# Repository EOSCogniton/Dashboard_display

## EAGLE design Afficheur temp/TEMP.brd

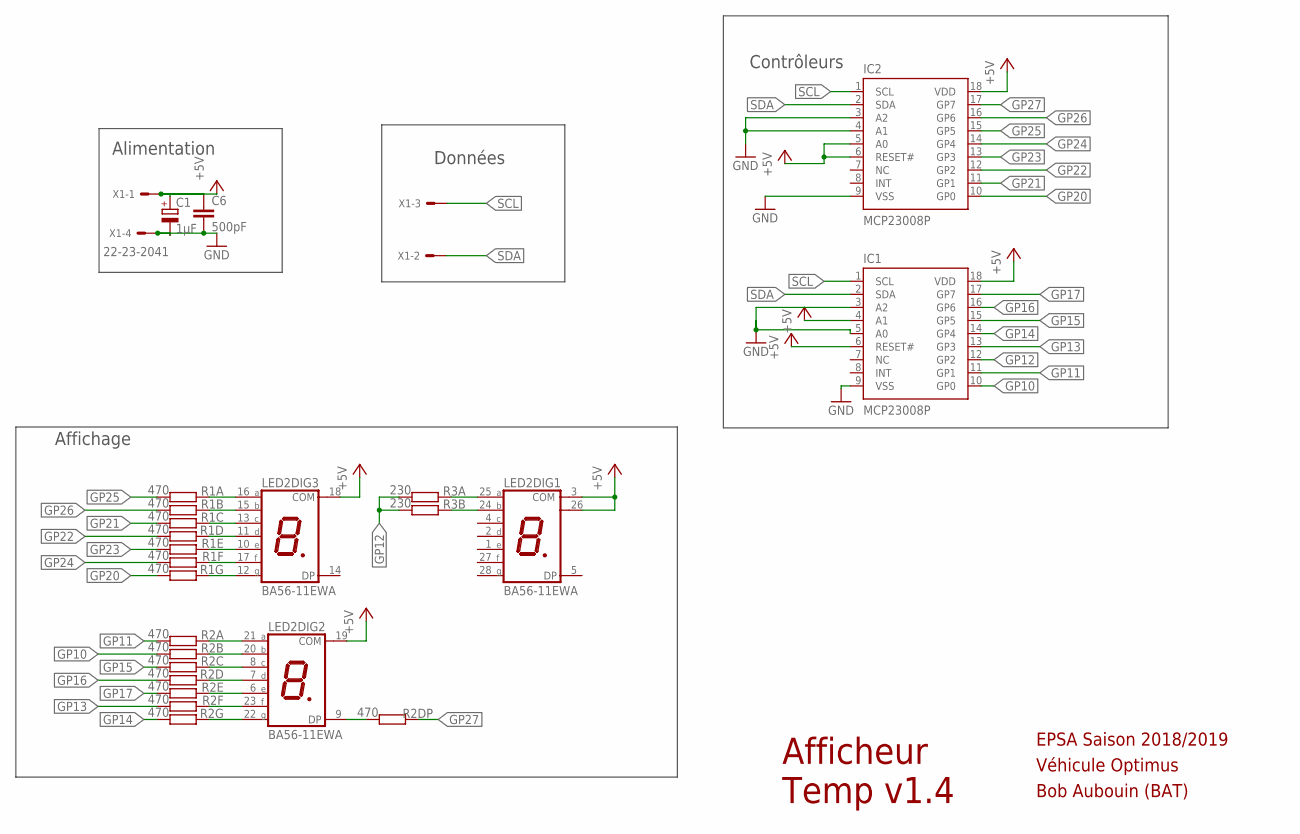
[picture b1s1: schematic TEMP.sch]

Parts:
C1: 1µF; B45181A
C6: 500pF; C025-025X050
IC1, IC2: MCP23008P; DIL18
LED2: BA56-11EWA; BA/BC56
R1A, R1B, R1C, R1D, R1E, R1F, R1G, R2A, R2B, R2C, R2D, R2DP, R2E, R2F, R2G: 470; 0204/7
R3A, R3B: 230; 0204/7
X1: 22-23-2041

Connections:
+5V: C1.+, C6.1, IC1.4 (A1), IC1.6 (RESET#), IC1.18 (VDD), IC2.5 (A0), IC2.6 (RESET#), IC2.18 (VDD), LED2.3 (COM), LED2.18 (COM), LED2.19 (COM), LED2.26 (COM), X1.1
GND: C1.-, C6.2, IC1.3 (A2), IC1.5 (A0), IC1.9 (VSS), IC2.3 (A2), IC2.4 (A1), IC2.9 (VSS), X1.4
GP10: IC1.10 (GP0), R2B.2
GP11: IC1.11 (GP1), R2A.2
GP12: IC1.12 (GP2), R3A.2, R3B.2
GP13: IC1.13 (GP3), R2F.2
GP14: IC1.14 (GP4), R2G.2
GP15: IC1.15 (GP5), R2C.2
GP16: IC1.16 (GP6), R2D.2
GP17: IC1.17 (GP7), R2E.2
GP20: IC2.10 (GP0), R1G.2
GP21: IC2.11 (GP1), R1C.2
GP22: IC2.12 (GP2), R1D.2
GP23: IC2.13 (GP3), R1E.2
GP24: IC2.14 (GP4), R1F.2
GP25: IC2.15 (GP5), R1A.2
GP26: IC2.16 (GP6), R1B.2
GP27: IC2.17 (GP7), R2DP.1
unnamed: LED2.16 (A), R1A.1
unnamed: LED2.15 (B), R1B.1
unnamed: LED2.13 (C), R1C.1
unnamed: LED2.11 (D), R1D.1
unnamed: LED2.10 (E), R1E.1
unnamed: LED2.17 (F), R1F.1
unnamed: LED2.12 (G), R1G.1
unnamed: LED2.21 (A), R2A.1
unnamed: LED2.20 (B), R2B.1
unnamed: LED2.8 (C), R2C.1
unnamed: LED2.7 (D), R2D.1
unnamed: LED2.6 (E), R2E.1
unnamed: LED2.23 (F), R2F.1
unnamed: LED2.22 (G), R2G.1
unnamed: LED2.9 (DP), R2DP.2
unnamed: LED2.24 (B), R3B.1
unnamed: LED2.25 (A), R3A.1
SCL: IC1.1 (SCL), IC2.1 (SCL), X1.3
SDA: IC1.2 (SDA), IC2.2 (SDA), X1.2

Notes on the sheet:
Afficheur Temp v1.4
EPSA Saison 2018/2019
Alimentation
Contrôleurs
Données
Affichage
Véhicule Optimus
Bob Aubouin (BAT)

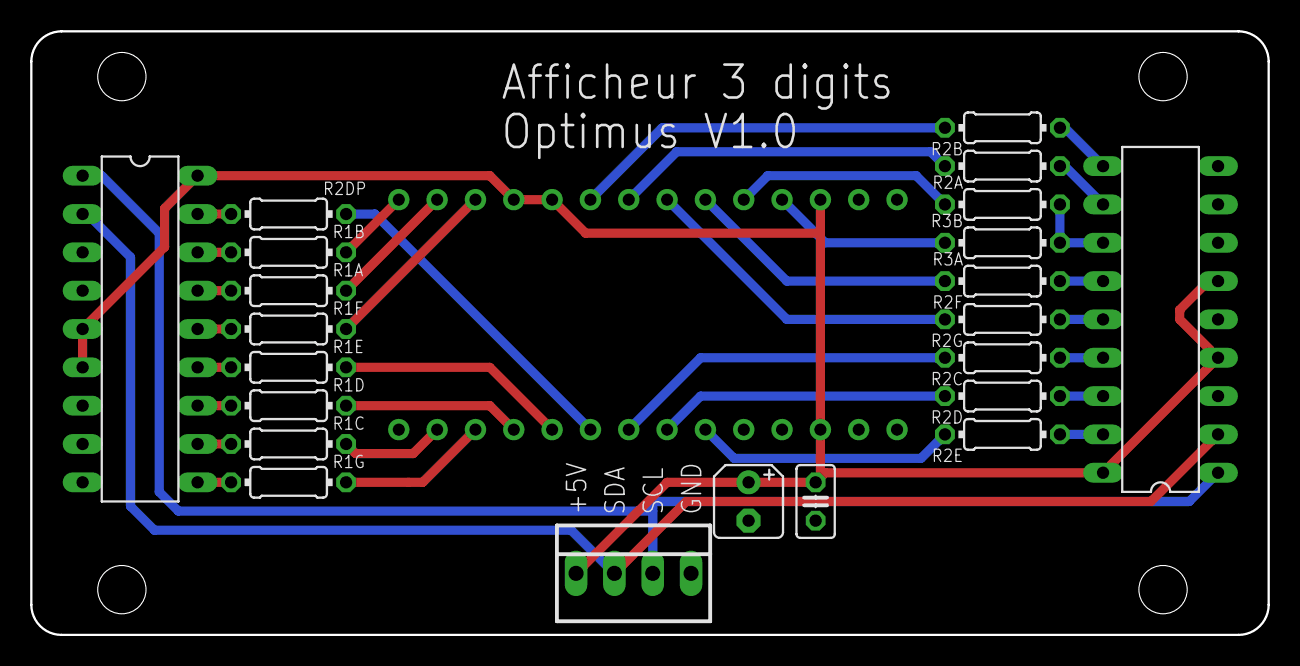
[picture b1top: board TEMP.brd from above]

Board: 2 copper layers, 82.0 x 40.0 mm, 23 parts (1 on the bottom side), 37 nets.

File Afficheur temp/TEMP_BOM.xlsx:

Qty | Value | Device | Description | Dispo au garage ? | Référence RS |  |  |  |  | oui
2 | 1k | R-EU_0204/7 | RESISTOR, European symbol | oui |  |  |  |  |  | non
1 |  | 22-23-2041 | .100 (2.54mm) Center Header - 4 Pin" | Je sais pas | 679-5596 |  |  |  |  | Je sais pas
2 | 230 | R-EU_0204/7 | RESISTOR, European symbol | oui
15 | 470 | R-EU_0204/7 | RESISTOR, European symbol | oui
1 | 500pF | C-EU025-025X050 | CAPACITOR, European symbol | Je sais pas | 831-3026
1 |  | BA56-11EWA | 14.22mm (0.56INCH) THREE DIGIT NUMERIC DISPLAY | oui
2 |  | MCP23008P | 8-Bit I/O Expander with I2C Interface | oui

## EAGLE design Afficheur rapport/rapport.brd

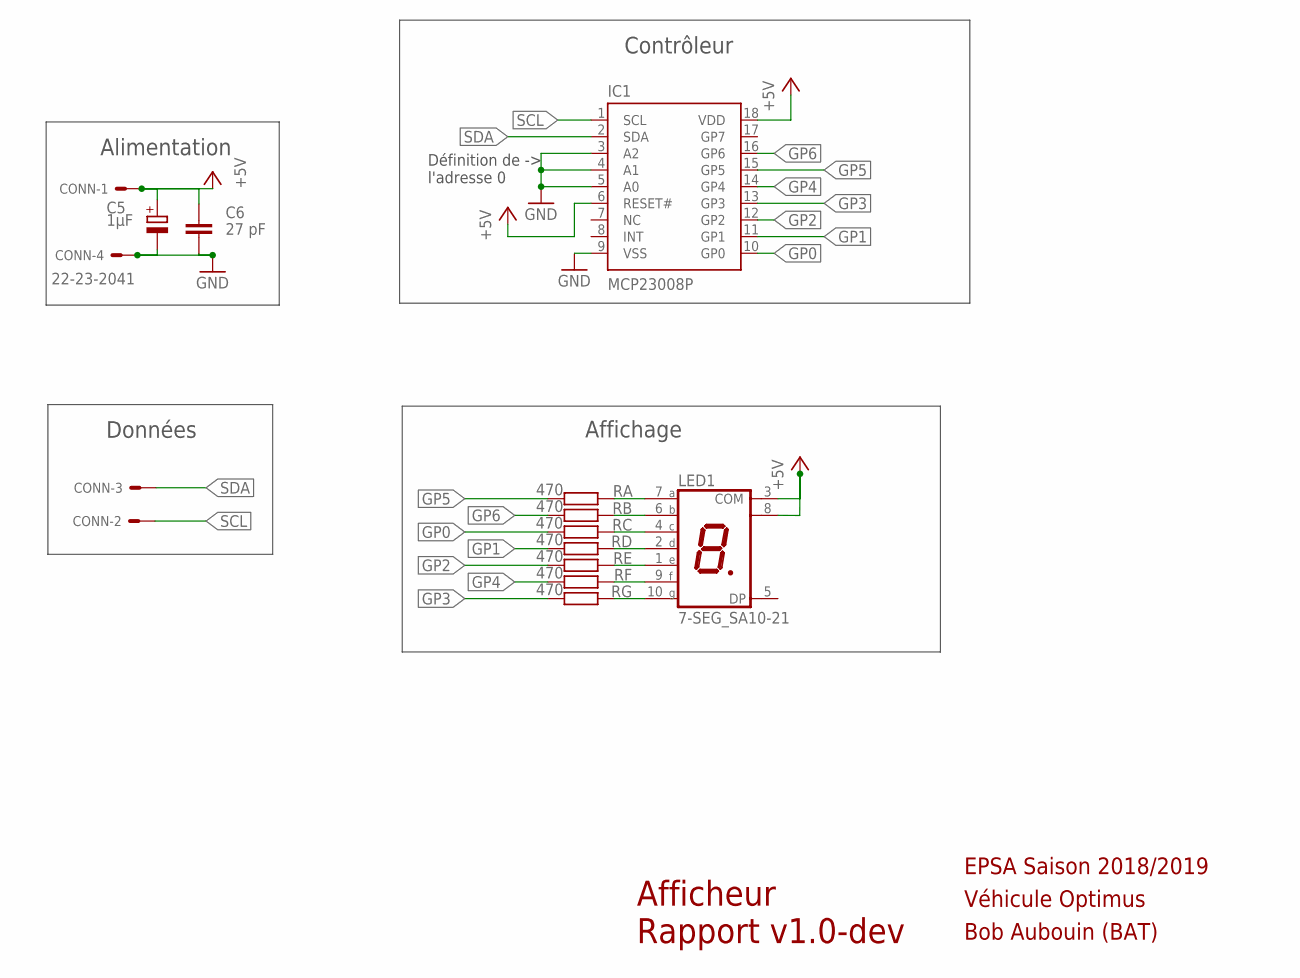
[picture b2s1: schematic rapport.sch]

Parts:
C5: 1µF; B45181A
C6: 27 pF; C025-025X050
CONN: 22-23-2041
IC1: MCP23008P; DIL18
LED1: 7-SEG_SA10-21; SA10-21
RA: 470; 0204/7
RB: 470; 0204/7
RC: 470; 0204/7
RD: 470; 0204/7
RE: 470; 0204/7
RF: 470; 0204/7
RG: 470; 0204/7

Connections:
+5V: C5.+, C6.1, CONN.1, IC1.6 (RESET#), IC1.18 (VDD), LED1.3 (COM), LED1.8 (COM)
GND: C5.-, C6.2, CONN.4, IC1.3 (A2), IC1.4 (A1), IC1.5 (A0), IC1.9 (VSS)
GP0: IC1.10 (GP0), RC.2
GP1: IC1.11 (GP1), RD.2
GP2: IC1.12 (GP2), RE.2
GP3: IC1.13 (GP3), RG.2
GP4: IC1.14 (GP4), RF.2
GP5: IC1.15 (GP5), RA.2
GP6: IC1.16 (GP6), RB.2
unnamed: LED1.10 (G), RG.1
unnamed: LED1.9 (F), RF.1
unnamed: LED1.1 (E), RE.1
unnamed: LED1.2 (D), RD.1
unnamed: LED1.4 (C), RC.1
unnamed: LED1.6 (B), RB.1
unnamed: LED1.7 (A), RA.1
SCL: CONN.2, IC1.1 (SCL)
SDA: CONN.3, IC1.2 (SDA)

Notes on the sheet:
Afficheur Rapport v1.0-dev
EPSA Saison 2018/2019
Alimentation
Contrôleur
Données
Affichage
Véhicule Optimus
Bob Aubouin (BAT)
Définition de -> l'adresse 0

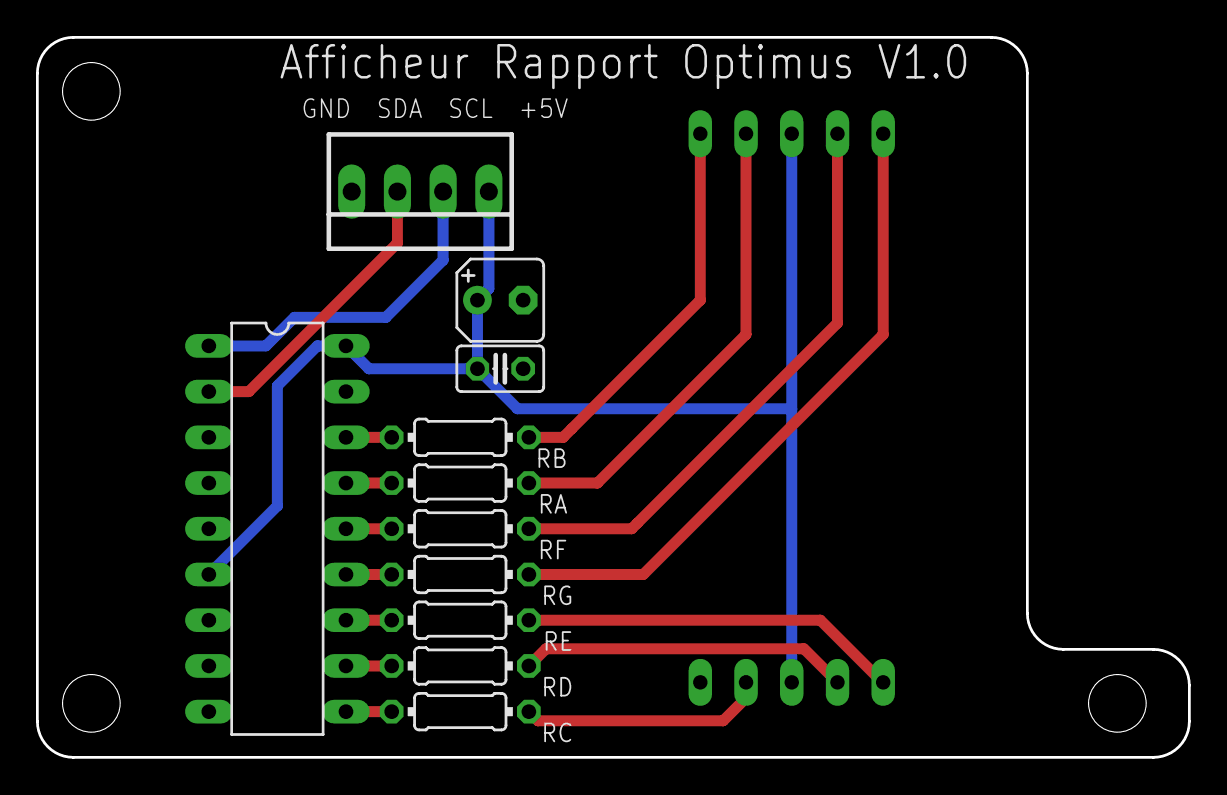
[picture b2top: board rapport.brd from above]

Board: 2 copper layers, 64.0 x 40.0 mm, 12 parts (1 on the bottom side), 18 nets.

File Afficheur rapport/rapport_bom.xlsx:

Qty | Value | Device | Description | Dispo au garage ? | Référence RS |  |  |  |  |  | oui
2 | 1k | R-EU_0204/7 | RESISTOR, European symbol | oui |  |  |  |  |  |  | non
1 |  | 22-23-2041 | .100 (2.54mm) Center Header - 4 Pin" | Je sais pas | 679-5596 |  |  |  |  |  | Je sais pas
7 | 470 | R-EU_0204/7 | RESISTOR, European symbol | oui
1 | 500pF | C-EU025-025X050 | CAPACITOR, European symbol | Je sais pas | 831-3026
1 |  | 7-SEG_SA10-21 | Kingbright 14.2mm (0.56 INCH) SINGLE DIGIT NUMERIC DUISPLAY | oui
1 |  | MCP23008P | 8-Bit I/O Expander with I2C Interface | oui

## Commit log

2018-12-07 travail déjà fait
2018-12-08 sérigraphie
2018-12-11 ajustement trou de maintien
2018-12-16 Ajout de la BOM
2018-12-16 suppression des résistance de pull-up, modification des condo
2018-12-16 Ajout des modification précédente sur le PCB
2018-12-18 Supprsion des résistance de pull-up et MAJ des condos de lissage
2018-12-18 Suppression des deux autres condos de lissages pour le Rapport
2018-12-18 Création des Fichier d'usinage
2018-12-18 Homogénéisation du schéma
2018-12-18 Mise en qualité
2019-01-13 Ajout des fichiers d'usinage et du readme
2019-01-19 Ajout du gitignore
2019-01-19 maj de la BOM
2019-01-19 Passage à la version de dev suivante
